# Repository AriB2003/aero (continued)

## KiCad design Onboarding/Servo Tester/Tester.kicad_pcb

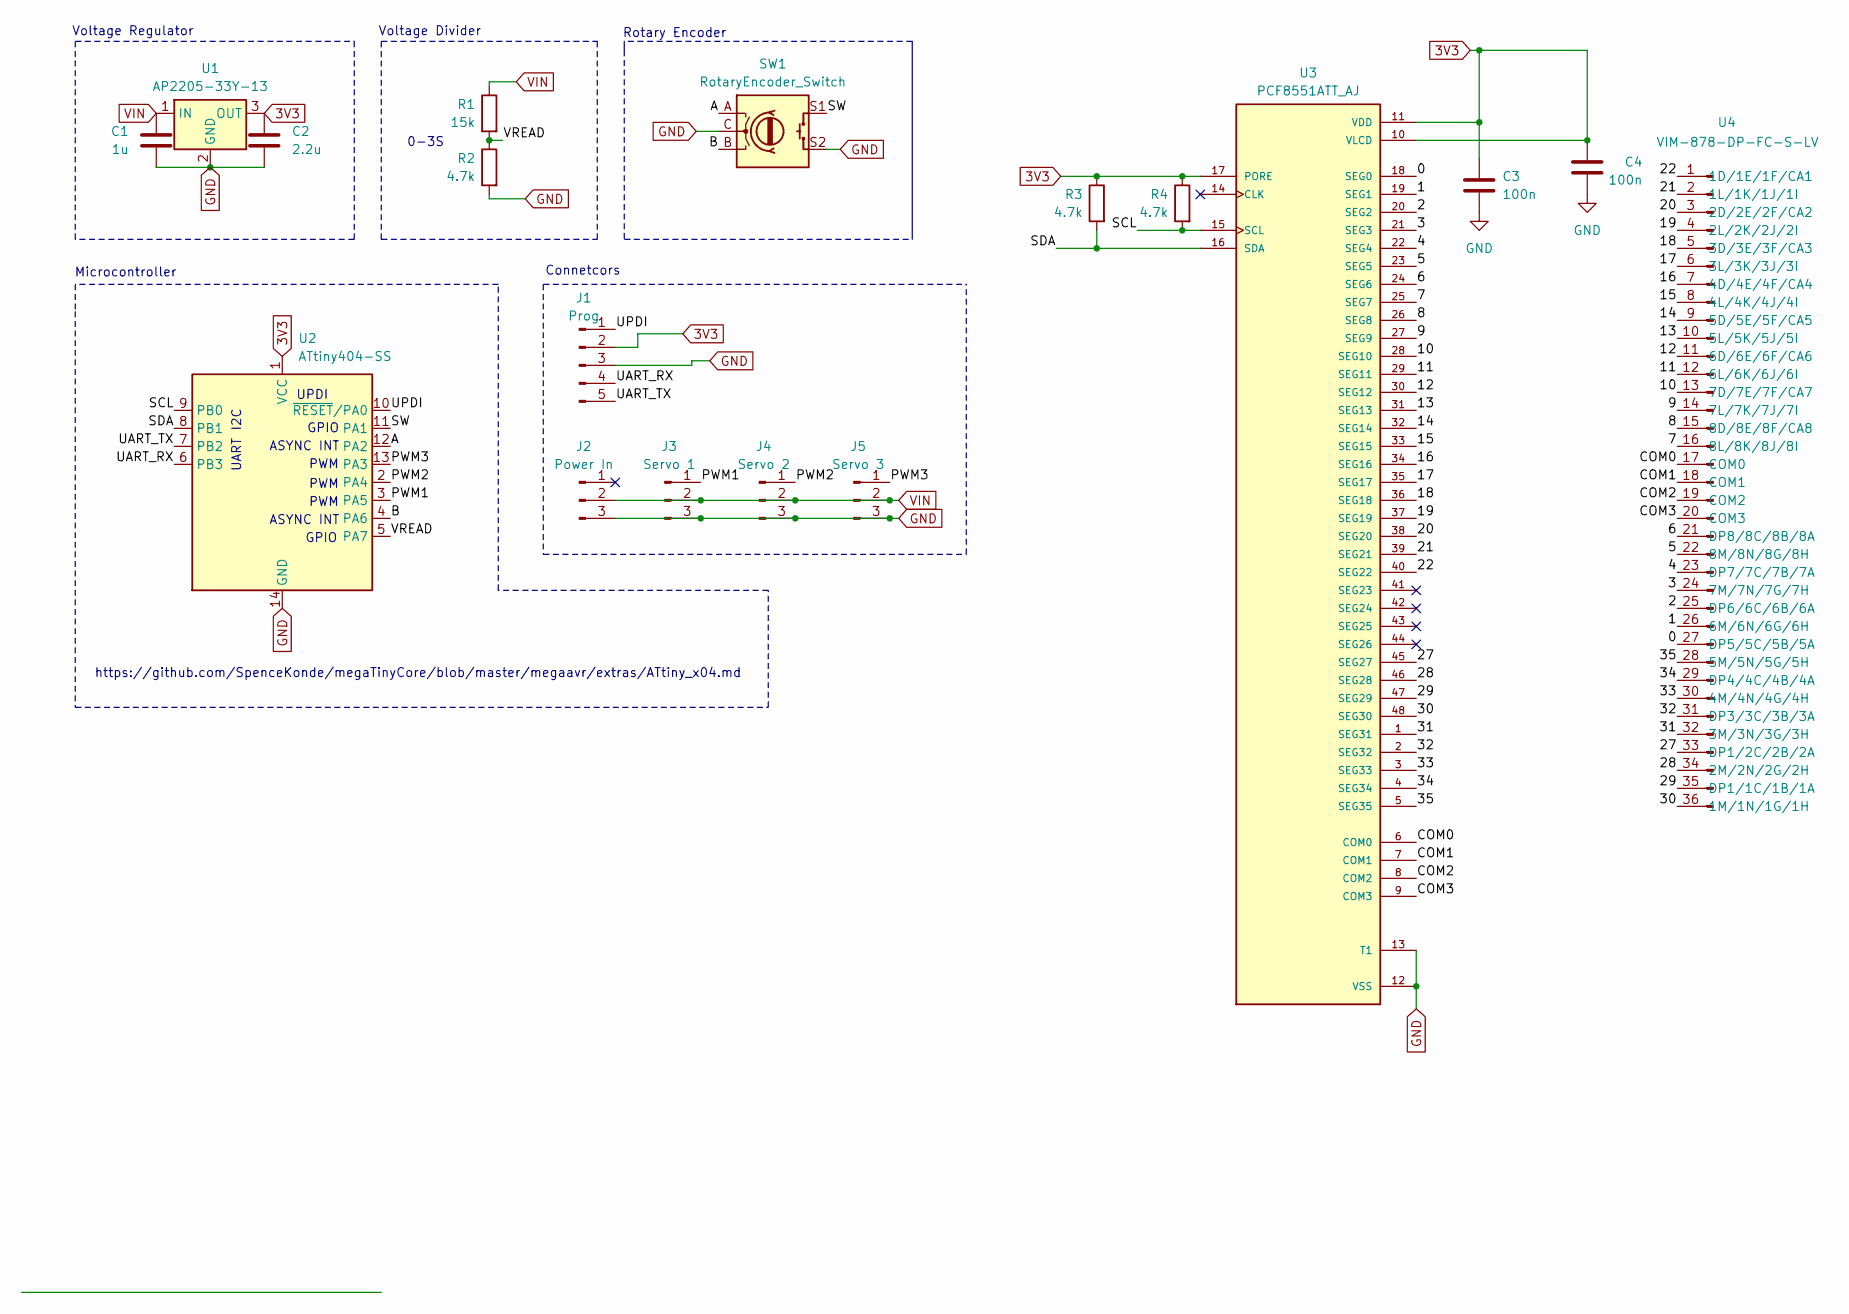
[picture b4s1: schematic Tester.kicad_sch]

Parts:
C1: 1u; C_0603_1608Metric_Pad1.08x0.95mm_HandSolder
C2: 2.2u; C_0603_1608Metric_Pad1.08x0.95mm_HandSolder
C3, C4: 100n; C_0603_1608Metric_Pad1.08x0.95mm_HandSolder
J1: Prog; PinSocket_1x05_P2.54mm_Vertical
J2: Power In; PinSocket_1x03_P2.54mm_Vertical
J3: Servo 1; PinSocket_1x03_P2.54mm_Vertical
J4: Servo 2; PinSocket_1x03_P2.54mm_Vertical
J5: Servo 3; PinSocket_1x03_P2.54mm_Vertical
R1: 15k; R_0603_1608Metric_Pad0.98x0.95mm_HandSolder
R2, R3, R4: 4.7k; R_0603_1608Metric_Pad0.98x0.95mm_HandSolder
SW1: RotaryEncoder_Switch; RotaryEncoder_Bourns_Vertical_PEC12R-3x17F-Sxxxx
U1: AP2205-33Y-13; SOT-89-3_Handsoldering
U2: ATtiny404-SS; SOIC-14_3.9x8.7mm_P1.27mm
U3: PCF8551ATT_AJ; SOP50P810X120-48N; PARTREV 2
U4: VIM-878-DP-FC-S-LV; VIM-878-DP

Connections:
3V3: C2.1, C3.1, C4.1, J1.2, R3.1, R4.1, U1.3 (OUT), U2.1 (VCC), U3.10 (VLCD), U3.11 (VDD), U3.17 (PORE)
/0: U3.18 (SEG0), U4.27 (DP5/5C/5B/5A)
/1: U3.19 (SEG1), U4.26 (6M/6N/6G/6H)
/2: U3.20 (SEG2), U4.25 (DP6/6C/6B/6A)
/3: U3.21 (SEG3), U4.24 (7M/7N/7G/7H)
/4: U3.22 (SEG4), U4.23 (DP7/7C/7B/7A)
/5: U3.23 (SEG5), U4.22 (8M/8N/8G/8H)
/6: U3.24 (SEG6), U4.21 (DP8/8C/8B/8A)
/7: U3.25 (SEG7), U4.16 (8L/8K/8J/8I)
/8: U3.26 (SEG8), U4.15 (8D/8E/8F/CA8)
/9: U3.27 (SEG9), U4.14 (7L/7K/7J/7I)
/10: U3.28 (SEG10), U4.13 (7D/7E/7F/CA7)
/11: U3.29 (SEG11), U4.12 (6L/6K/6J/6I)
/12: U3.30 (SEG12), U4.11 (6D/6E/6F/CA6)
/13: U3.31 (SEG13), U4.10 (5L/5K/5J/5I)
/14: U3.32 (SEG14), U4.9 (5D/5E/5F/CA5)
/15: U3.33 (SEG15), U4.8 (4L/4K/4J/4I)
/16: U3.34 (SEG16), U4.7 (4D/4E/4F/CA4)
/17: U3.35 (SEG17), U4.6 (3L/3K/3J/3I)
/18: U3.36 (SEG18), U4.5 (3D/3E/3F/CA3)
/19: U3.37 (SEG19), U4.4 (2L/2K/2J/2I)
/20: U3.38 (SEG20), U4.3 (2D/2E/2F/CA2)
/21: U3.39 (SEG21), U4.2 (1L/1K/1J/1I)
/22: U3.40 (SEG22), U4.1 (1D/1E/1F/CA1)
/27: U3.45 (SEG27), U4.33 (DP1/2C/2B/2A)
/28: U3.46 (SEG28), U4.34 (2M/2N/2G/2H)
/29: U3.47 (SEG29), U4.35 (DP1/1C/1B/1A)
/30: U3.48 (SEG30), U4.36 (1M/1N/1G/1H)
/31: U3.1 (SEG31), U4.32 (3M/3N/3G/3H)
/32: U3.2 (SEG32), U4.31 (DP3/3C/3B/3A)
/33: U3.3 (SEG33), U4.30 (4M/4N/4G/4H)
/34: U3.4 (SEG34), U4.29 (DP4/4C/4B/4A)
/35: U3.5 (SEG35), U4.28 (5M/5N/5G/5H)
/A: SW1.A, U2.12 (PA2)
/B: SW1.B, U2.4 (PA6)
/COM0: U3.6 (COM0), U4.17 (COM0)
/COM1: U3.7 (COM1), U4.18 (COM1)
/COM2: U3.8 (COM2), U4.19 (COM2)
/COM3: U3.9 (COM3), U4.20 (COM3)
/PWM1: J3.1, U2.3 (PA5)
/PWM2: J4.1, U2.2 (PA4)
/PWM3: J5.1, U2.13 (PA3)
/SCL: R4.2, U2.9 (PB0), U3.15 (SCL)
/SDA: R3.2, U2.8 (PB1), U3.16 (SDA)
/SW: SW1.S1, U2.11 (PA1)
/UART_RX: J1.4, U2.6 (PB3)
/UART_TX: J1.5, U2.7 (PB2)
/UPDI: J1.1, U2.10 (~RESET/PA0)
/VREAD: R1.2, R2.1, U2.5 (PA7)
GND: C1.2, C2.2, C3.2, C4.2, J1.3, J2.3, J3.3, J4.3, J5.3, R2.2, SW1.C, SW1.S2, U1.2 (GND), U2.14 (GND), U3.12 (VSS), U3.13 (T1)
VIN: C1.1, J2.2, J3.2, J4.2, J5.2, R1.1, U1.1 (IN)

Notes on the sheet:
GPIO
Voltage Divider
Connetcors
ASYNC INT
https://github.com/SpenceKonde/megaTinyCore/blob/master/megaavr/extras/ATtiny_x04.md
PWM
0-3S
Microcontroller
I2C
UPDI
Voltage Regulator
UART
Rotary Encoder

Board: 2 copper layers, 18 parts (1 on the bottom side), 51 nets, no tracks yet.

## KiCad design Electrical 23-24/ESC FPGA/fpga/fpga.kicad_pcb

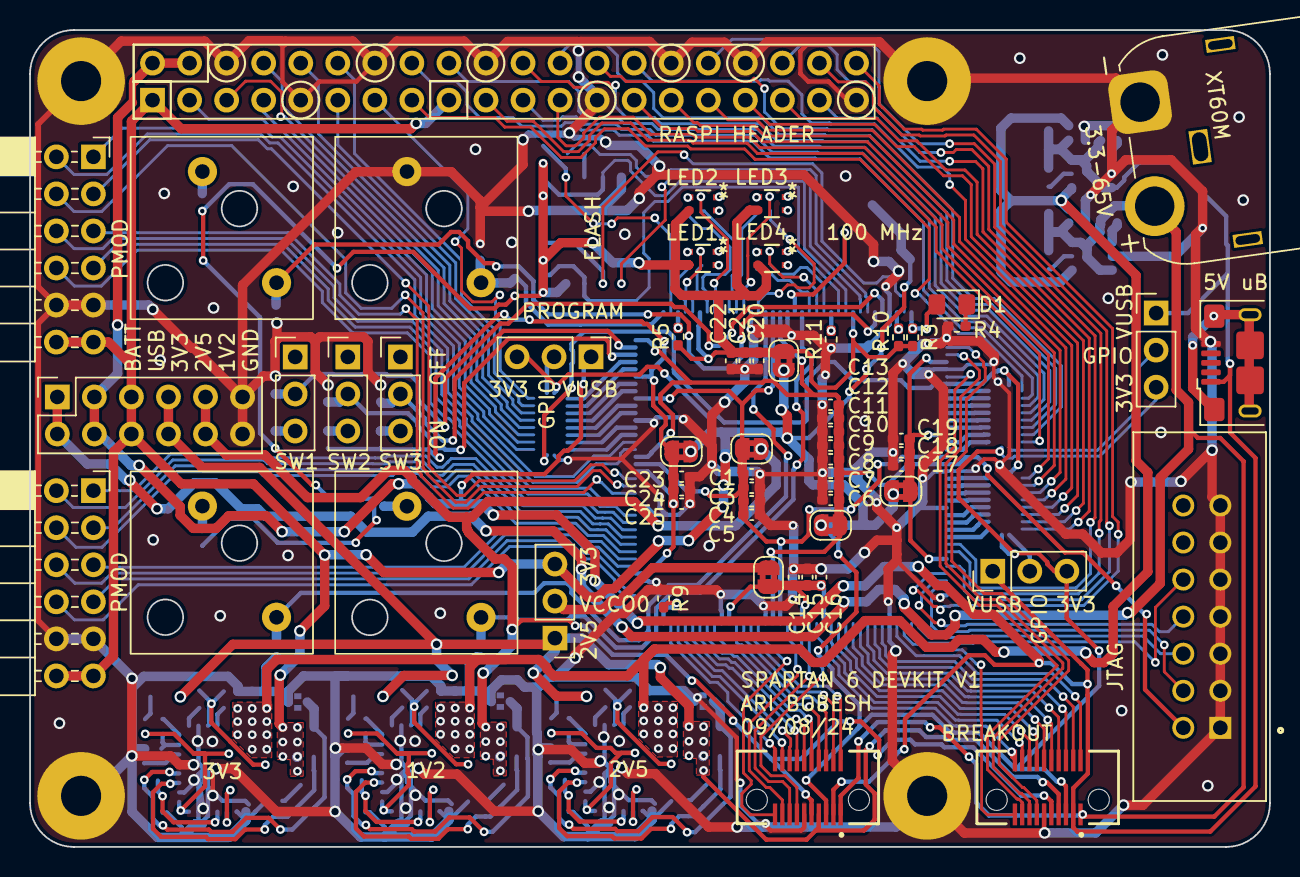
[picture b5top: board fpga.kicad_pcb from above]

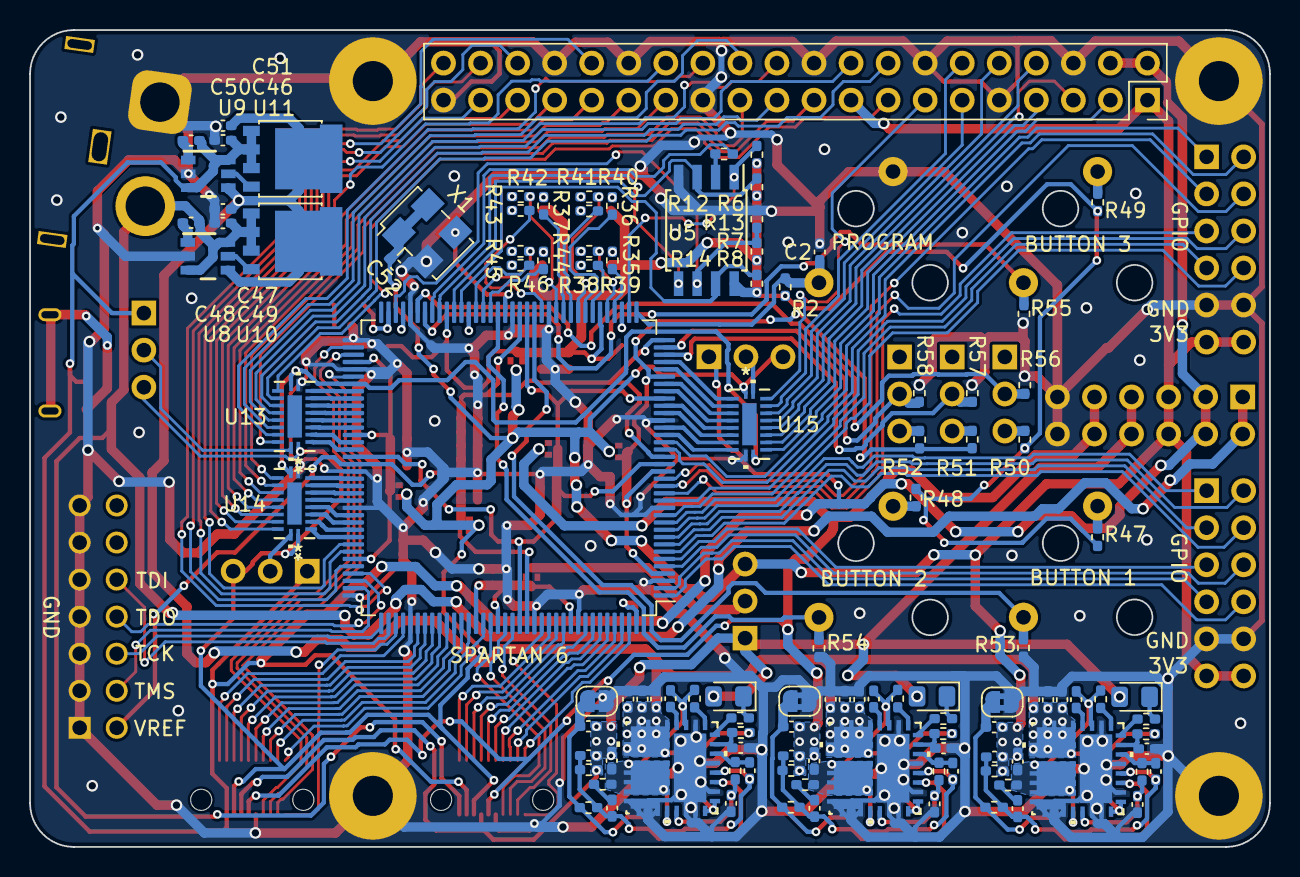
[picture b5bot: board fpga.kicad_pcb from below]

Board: 2 copper layers, 85.0 x 56.0 mm, 174 parts (113 on the bottom side), 206 nets.

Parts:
C1, C2, C3, C4, C6, C7, C8, C9, C10, C11, C12, C14, C17, C20, C23: 4.7u; C_0402_1005Metric_Pad0.74x0.62mm_HandSolder
C5, C13, C15, C16, C18, C19, C21, C22, C24, C25: 0.47u; C_0402_1005Metric_Pad0.74x0.62mm_HandSolder
C26, C33, C36, C43, C53, C60: 0.1u; C_0402_1005Metric_Pad0.74x0.62mm_HandSolder
C27, C28, C29, C37, C38, C39, C54, C55, C56: 2.2u HV; C_0402_1005Metric_Pad0.74x0.62mm_HandSolder
C30, C42, C47, C51, C59: 1u HV; C_0402_1005Metric_Pad0.74x0.62mm_HandSolder
C31, C32, C40, C41, C57, C58: 2.2u; C_0402_1005Metric_Pad0.74x0.62mm_HandSolder
C34, C44, C61: 4.7n; C_0402_1005Metric_Pad0.74x0.62mm_HandSolder
C35, C45, C62: 47u; C_0402_1005Metric_Pad0.74x0.62mm_HandSolder
C46, C49: 22n HV; C_0402_1005Metric_Pad0.74x0.62mm_HandSolder
C48, C50: 0.1u HV; C_0402_1005Metric_Pad0.74x0.62mm_HandSolder
C52: 0.01uF; C_0402_1005Metric_Pad0.74x0.62mm_HandSolder
D1, D2, D3, D4: LED; LED_0805_2012Metric_Pad1.15x1.40mm_HandSolder
J1: SBH11-PBPC-D07-ST-BK; SULLINS_SBH11-PBPC-D07-ST-BK
J2, J4: LSHM-110-04.0-L-DV-A-N-K-TR; SAMTEC_LSHM-110-04.0-L-DV-A-N-K-TR
J3: USB_B_Micro; USB_Micro-B_Amphenol_10118193-0001LF_Horizontal
J5, J6: Conn_02x06_Top_Bottom; PinSocket_2x06_P2.54mm_Horizontal
J7: Conn_02x20_Odd_Even; PinSocket_2x20_P2.54mm_Vertical
J8: Conn_02x06_Top_Bottom; PinSocket_2x06_P2.54mm_Vertical
J9: Conn_01x01_Pin; RASPI
JP1, JP2, JP3, JP4, JP5, JP6, JP7, JP8, JP9: SolderJumper_2_Bridged; SolderJumper-2_P1.3mm_Bridged2Bar_RoundedPad1.0x1.5mm
L1: 3.9u; L_0402_1005Metric_Pad0.77x0.64mm_HandSolder
L2, L3: 1.5u; L_0402_1005Metric_Pad0.77x0.64mm_HandSolder
LED1, LED2, LED3, LED4: B38G3RGB-10D0003H2U1930; B38G3RGB-10D0003H2U1930_HVK
R1, R15, R22: 1.5k; R_0402_1005Metric_Pad0.72x0.64mm_HandSolder
R2, R5: 4.7k; R_0402_1005Metric_Pad0.72x0.64mm_HandSolder
R3, R4: 330; R_0402_1005Metric_Pad0.72x0.64mm_HandSolder
R6, R21: 2.2k; R_0402_1005Metric_Pad0.72x0.64mm_HandSolder
R7, R8: 100k; R_0402_1005Metric_Pad0.72x0.64mm_HandSolder
R9, R10, R11, R13, R14, R19, R20, R27, R28, R32, R34, R53, R54, R55, R56, R57, R58: 10k; R_0402_1005Metric_Pad0.72x0.64mm_HandSolder
R12, R16, R17, R23, R25, R29, R31: 2.2; R_0402_1005Metric_Pad0.72x0.64mm_HandSolder
R18, R24, R30: 82; R_0402_1005Metric_Pad0.72x0.64mm_HandSolder
R26: 7.5k; R_0402_1005Metric_Pad0.72x0.64mm_HandSolder
R33: 3.3k; R_0402_1005Metric_Pad0.72x0.64mm_HandSolder
R35, R36, R37, R44: 270; R_0402_1005Metric_Pad0.72x0.64mm_HandSolder
R38, R39, R40, R41, R42, R43, R45, R46: 56; R_0402_1005Metric_Pad0.72x0.64mm_HandSolder
R47, R48, R49, R50, R51, R52: 1k; R_0402_1005Metric_Pad0.72x0.64mm_HandSolder
SW1, SW3, SW4, SW5, SW9, SW10, SW11: SW_SPDT; PinHeader_1x03_P2.54mm_Vertical
SW2, SW6, SW7, SW8: SW_Push; NCA1
U1: XC6SLX9-TQG144; TQFP-144_20x20mm_P0.5mm
U5: MT25QL128ABA1ESE; SOIC-8W_5.3x5.3mm_P1.27mm
U6, U7, U12: MIC28515T-E/PHA; VQFN32_PHA_MCH
U8, U9: LM74700QDBVRQ1; DBV0006A_N
U10, U11: LFPAK56
U13, U14, U15: FXMA108BQX; WQFN20_2P5X4P5_ONS
X1: KC5032Z100.000C1JX00; Oscillator_SMD_EuroQuartz_XO53-4Pin_5.0x3.2mm_HandSoldering
XT60M: XT60M; AMASS_XT60IPW-M_1x03_P7.20mm_Horizontal

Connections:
1V2: C44.1, C45.1, J2.09, J4.09, J8.9, J8.10, JP7.1 (A), L2.2, R27.1
2V5: C61.1, C62.1, D2.2 (A), D3.2 (A), D4.2 (A), J2.07, J4.07, J8.7, J8.8, L3.2, R33.1, SW1.1 (A)
3V3: C34.1, C35.1, C52.2, J2.05, J4.05, J5.11, J5.12, J6.11, J6.12, J7.1, J7.17, J8.5, J8.6, JP4.1 (A), JP5.1 (A), JP6.1 (A), JP8.1 (A), L1.2, R20.1, SW1.3 (C), SW3.3 (C), SW4.3 (C), SW5.3 (C), U13.1 (VCCA), U14.1 (VCCA), U15.1 (VCCA), X1.1 (EN), X1.4 (Vdd)
/Bank1/HSWAPEN: R9.2, U1.144 (IO_L1P_HSWAPEN_0)
/Bank2/B1: R39.2, U1.43 (IO_L62N_D6_2)
/Bank2/B2: R41.2, U1.46 (IO_L49P_D3_2)
/Bank2/B3: R43.2, U1.50 (IO_L31N_GCLK30_D15_2)
/Bank2/B4: R46.2, U1.59 (IO_L13N_D10_2)
/Bank2/BTN1: R53.2, SW6.1, U1.51 (IO_L31P_GCLK31_D14_2)
/Bank2/BTN2: R54.2, SW7.1, U1.56 (IO_L30P_GCLK1_D13_2)
/Bank2/BTN3: R55.2, SW8.1, U1.66 (IO_L2N_CMPMOSI_2)
/Bank2/G1: R38.2, U1.41 (IO_L64P_D8_2)
/Bank2/G2: R40.2, U1.45 (IO_L49N_D4_2)
/Bank2/G3: R42.2, U1.48 (IO_L48P_D7_2)
/Bank2/G4: R45.2, U1.58 (IO_L14P_D11_2)
/Bank2/INIT_B_IO: R5.2, U1.39 (IO_L65P_INIT_B_2)
/Bank2/M0_IO: R10.2, U1.69 (IO_L1N_M0_CMPMISO_2)
/Bank2/M1_IO: R11.2, U1.60 (IO_L13P_M1_2)
/Bank2/OSCI: U1.55 (IO_L30N_GCLK0_USERCCLK_2), X1.3 (OUT)
/Bank2/R1: R35.2, U1.40 (IO_L64N_D9_2)
/Bank2/R2: R36.2, U1.44 (IO_L62P_D5_2)
/Bank2/R3: R37.2, U1.47 (IO_L48N_RDWR_B_VREF_2)
/Bank2/R4: R44.2, U1.57 (IO_L14N_D12_2)
/Bank2/SPI_MISO1_IO: R12.2, U1.65 (IO_L3P_D0_DIN_MISO_MISO1_2)
/Bank2/SW1: R56.2, SW9.2 (B), U1.67 (IO_L2P_CMPCLK_2)
/Bank2/SW2: R57.2, SW10.2 (B), U1.34 (IO_L1N_VREF_3)
/Bank2/SW3: R58.2, SW11.2 (B), U1.35 (IO_L1P_3)
/Program/DONE: D1.2 (A), R3.1, U1.71 (DONE_2)
/Regulators/FB1: C33.2, C34.2, R20.2, R21.1, U6.27 (FB)
/Regulators/FB2: C43.2, C44.2, R27.2, R28.1, U7.27 (FB)
/Regulators/FB3: C60.2, C61.2, R33.2, R34.1, U12.27 (FB)
/Regulators/SW1: C26.1, L1.1, R15.1, R19.1, U6.3 (SW), U6.12 (SW), U6.13 (SW), U6.14 (SW), U6.15 (SW), U6.20 (SW)
/Regulators/SW2: C36.1, L2.1, R22.1, R26.1, U7.3 (SW), U7.12 (SW), U7.13 (SW), U7.14 (SW), U7.15 (SW), U7.20 (SW)
/Regulators/SW3: C53.1, L3.1, R1.1, R32.1, U12.3 (SW), U12.12 (SW), U12.13 (SW), U12.14 (SW), U12.15 (SW), U12.20 (SW)
/Regulators/VDD1: C32.2, R17.2, U6.30 (VDD)
/Regulators/VDD2: C41.2, R23.2, U7.30 (VDD)
/Regulators/VIN: C27.2, C28.2, C29.2, C37.2, C38.2, C39.2, C47.1, C51.1, C54.2, C55.2, C56.2, R16.2, R25.2, R31.2, U6.5 (VIN), U6.6 (VIN), U6.7 (VIN), U6.8 (VIN), U6.9 (VIN), U6.10 (VIN), U6.11 (VIN), U6.24 (EN), U6.25 (FREQ), U7.5 (VIN), U7.6 (VIN), U7.7 (VIN), U7.8 (VIN), U7.9 (VIN), U7.10 (VIN), U7.11 (VIN), U7.24 (EN), U7.25 (FREQ), U8.4 (CATHODE), U9.4 (CATHODE), U10.5 (D), U11.5 (D), U12.5 (VIN), U12.6 (VIN), U12.7 (VIN), U12.8 (VIN), U12.9 (VIN), U12.10 (VIN), U12.11 (VIN), U12.24 (EN), U12.25 (FREQ)
GND: C1.2, C2.2, C3.2, C4.2, C5.2, C6.2, C7.2, C8.2, C9.2, C10.2, C11.2, C12.2, C13.2, C14.2, C15.2, C16.2, C17.2, C18.2, C19.2, C20.2, C21.2, C22.2, C23.2, C24.2, C25.2, C27.1, C28.1, C29.1, C30.1, C31.1, C37.1, C38.1, C39.1, C40.1, C42.1, C46.2, C47.2, C49.2, C51.2, C52.1, C54.1, C55.1, C56.1, C57.1, C59.1, J1.1, J1.3, J1.5, J1.7, J1.9, J1.11, J1.13, J2.11, J3.5 (GND), J4.11, J5.9, J5.10, J6.9, J6.10, J7.6, J7.9, J7.14, J7.20, J7.25, J7.30, J7.34, J7.39, J8.11, J8.12, J9.1, JP1.2 (B), JP2.2 (B), JP3.2 (B), R4.2, R7.1, R9.1, R11.1, R53.1, R54.1, R55.1, R56.1, R57.1, R58.1, SW2.2, U1.3 (GND), U1.13 (GND), U1.25 (GND), U1.49 (GND), U1.54 (GND), U1.68 (GND), U1.73 (SUSPEND), U1.77 (GND), U1.91 (GND), U1.96 (GND), U1.108 (GND), U1.113 (GND), U1.130 (GND), U1.136 (GND), U5.4 (VSS), U6.2 (PGND), U6.16 (PGND), U6.17 (PGND), U6.18 (PGND), U6.19 (PGND), U6.22 (PGND), U6.23 (EXTVDD), U6.26 (MODE), U6.29 (PGND), U6.33 (PGND), U7.2 (PGND), U7.16 (PGND), U7.17 (PGND), U7.18 (PGND), U7.19 (PGND), U7.22 (PGND), U7.23 (EXTVDD), U7.26 (MODE), U7.29 (PGND), U7.33 (PGND), U8.2 (GND), U9.2 (GND), U12.2 (PGND), U12.16 (PGND), U12.17 (PGND), U12.18 (PGND), U12.19 (PGND), U12.22 (PGND), U12.23 (EXTVDD), U12.26 (MODE), U12.29 (PGND), U12.33 (PGND), U13.10 (GND), U14.10 (GND), U15.10 (GND), X1.2 (GND), XT60M.1 (-)
GND1: C32.1, C35.2, JP1.1 (A), R21.2, U6.28 (AGND)
GND2: C41.1, C45.2, JP2.1 (A), R28.2, U7.28 (AGND)
GND3: C58.1, C62.2, JP3.1 (A), R34.2, U12.28 (AGND)
GPIO0: J7.27, U14.13 (B6)
GPIO1: J7.28, U14.16 (B3)
GPIO2: J7.3, U15.12 (B7)
GPIO3: J7.5, U15.14 (B5)
GPIO4: J7.7, U15.13 (B6)
GPIO5: J7.29, U14.14 (B5)
GPIO6: J7.31, U14.15 (B4)
GPIO7: J7.26, U13.18 (B1)
GPIO8: J7.24, U13.17 (B2)
GPIO9: J7.21, U13.14 (B5)
GPIO10: J7.19, U13.19 (B0)
GPIO11: J7.23, U14.12 (B7)
GPIO12: J7.32, U1.102 (IO_L32P_1)
GPIO13: J7.33, U14.17 (B2)
GPIO14: J7.8, U15.15 (B4)
GPIO15: J7.10, U15.16 (B3)
GPIO16: J7.36, U1.101 (IO_L32N_1)
GPIO17: J7.11, U15.17 (B2)
GPIO18: J7.12, U15.18 (B1)
GPIO19: J7.35, U14.18 (B1)
GPIO20: J7.38, U1.104 (IO_L1N_VREF_1)
GPIO21: J7.40, U1.105 (IO_L1P_1)
GPIO22: J7.15, U13.12 (B7)
GPIO23: J7.16, U13.13 (B6)
GPIO24: J7.18, U13.15 (B4)
GPIO25: J7.22, U13.16 (B3)
GPIO26: J7.37, U14.19 (B0)
GPIO27: J7.13, U15.19 (B0)
unnamed: C33.1, R19.2
unnamed: C43.1, R26.2
unnamed: C60.1, R32.2
unnamed: D1.1 (K), R4.1
unnamed: D2.1 (K), R18.1
unnamed: D3.1 (K), R24.1
unnamed: D4.1 (K), R30.1
unnamed: JP9.2 (B), SW1.2 (B)
unnamed: LED1.1, R38.1
unnamed: LED1.2, R39.1
unnamed: LED1.4, R35.1
unnamed: LED2.1, R40.1
unnamed: LED2.2, R41.1
unnamed: LED2.4, R36.1
unnamed: LED3.1, R42.1
unnamed: LED3.2, R43.1
unnamed: LED3.4, R37.1
unnamed: LED4.1, R45.1
unnamed: LED4.2, R46.1
unnamed: LED4.4, R44.1
unnamed: R47.1, SW6.2
unnamed: R48.1, SW7.2
unnamed: R49.1, SW8.2
unnamed: SW3.2 (B), U13.20 (VCCB)
unnamed: SW4.2 (B), U14.20 (VCCB)
unnamed: SW5.2 (B), U15.20 (VCCB)
unnamed: R50.1, SW9.3 (C)
unnamed: R51.1, SW10.3 (C)
unnamed: R52.1, SW11.3 (C)
unnamed: J2.20, U1.143 (IO_L1N_VREF_0)
unnamed: J2.16, U1.141 (IO_L2N_0)
unnamed: J2.18, U1.142 (IO_L2P_0)
unnamed: J2.12, U1.139 (IO_L3N_0)
unnamed: J2.14, U1.140 (IO_L3P_0)
unnamed: J2.08, U1.137 (IO_L4N_0)
unnamed: J2.10, U1.138 (IO_L4P_0)
unnamed: J2.04, U1.133 (IO_L34N_GCLK18_0)
unnamed: J2.06, U1.134 (IO_L34P_GCLK19_0)
unnamed: J2.19, U1.131 (IO_L35N_GCLK16_0)
unnamed: J2.02, U1.132 (IO_L35P_GCLK17_0)
unnamed: J2.15, U1.126 (IO_L36N_GCLK14_0)
unnamed: J2.17, U1.127 (IO_L36P_GCLK15_0)
unnamed: J4.20, U1.123 (IO_L37N_GCLK12_0)
unnamed: J2.13, U1.124 (IO_L37P_GCLK13_0)
unnamed: J4.17, U1.78 (IO_L47N_1)
unnamed: J4.16, U1.120 (IO_L62N_VREF_0)
unnamed: J4.18, U1.121 (IO_L62P_0)
unnamed: J4.12, U1.118 (IO_L63N_SCP6_0)
unnamed: J4.14, U1.119 (IO_L63P_SCP7_0)
unnamed: J4.08, U1.116 (IO_L64N_SCP4_0)
unnamed: J4.10, U1.117 (IO_L64P_SCP5_0)
unnamed: J4.04, U1.114 (IO_L65N_SCP2_0)
unnamed: J4.06, U1.115 (IO_L65P_SCP3_0)
unnamed: J4.19, U1.111 (IO_L66N_SCP0_0)
unnamed: J4.02, U1.112 (IO_L66P_SCP1_0)
unnamed: J4.13, U1.74 (IO_L74N_DOUT_BUSY_1)
unnamed: J4.15, U1.75 (IO_L74P_AWAKE_1)
unnamed: C2.1, R2.2, SW2.1, U1.37 (PROGRAM_B_2)
unnamed: C26.2, U6.4 (BST)
unnamed: R15.2, U6.1 (ILIM)
unnamed: R18.2, U6.32 (PG)
unnamed: C31.2, R17.1, U6.21 (PVDD)
unnamed: C30.2, R16.1, U6.31 (SVIN)
unnamed: C36.2, U7.4 (BST)
unnamed: R22.2, U7.1 (ILIM)
unnamed: R24.2, U7.32 (PG)
unnamed: C40.2, R23.1, U7.21 (PVDD)
unnamed: C42.2, R25.1, U7.31 (SVIN)
unnamed: C48.2, U8.1 (VCAP)
unnamed: C50.2, U9.1 (VCAP)
unnamed: U8.5 (GATE), U10.4 (G)
unnamed: U9.5 (GATE), U11.4 (G)
unnamed: C53.2, U12.4 (BST)
unnamed: R1.2, U12.1 (ILIM)
unnamed: R30.2, U12.32 (PG)
unnamed: C57.2, R29.1, U12.21 (PVDD)
unnamed: C59.2, R31.1, U12.31 (SVIN)
unnamed: C58.2, R29.2, U12.30 (VDD)
unnamed: U1.88 (IO_L42P_GCLK7_1), U13.2 (A0)
unnamed: U1.87 (IO_L42N_GCLK6_TRDY1_1), U13.3 (A1)
unnamed: U1.85 (IO_L43P_GCLK5_1), U13.4 (A2)
unnamed: U1.84 (IO_L43N_GCLK4_1), U13.5 (A3)
unnamed: U1.83 (IO_L45P_1), U13.6 (A4)
unnamed: U1.82 (IO_L45N_1), U13.7 (A5)
unnamed: U1.81 (IO_L46P_1), U13.8 (A6)
unnamed: U1.80 (IO_L46N_1), U13.9 (A7)
unnamed: U1.100 (IO_L33P_1), U14.2 (A0)
unnamed: U1.99 (IO_L33N_1), U14.3 (A1)
unnamed: U1.98 (IO_L34P_1), U14.4 (A2)
unnamed: U1.97 (IO_L34N_1), U14.5 (A3)
unnamed: U1.95 (IO_L40P_GCLK11_1), U14.6 (A4)
unnamed: U1.94 (IO_L40N_GCLK10_1), U14.7 (A5)
unnamed: U1.93 (IO_L41P_GCLK9_IRDY1_1), U14.8 (A6)
unnamed: U1.92 (IO_L41N_GCLK8_1), U14.9 (A7)
unnamed: U1.33 (IO_L2P_3), U15.2 (A0)
unnamed: U1.32 (IO_L2N_3), U15.3 (A1)
unnamed: U1.30 (IO_L36P_3), U15.4 (A2)
unnamed: U1.29 (IO_L36N_3), U15.5 (A3)
unnamed: U1.27 (IO_L37P_3), U15.6 (A4)
unnamed: U1.26 (IO_L37N_3), U15.7 (A5)
unnamed: U1.24 (IO_L41P_GCLK27_3), U15.8 (A6)
unnamed: U1.23 (IO_L41N_GCLK26_3), U15.9 (A7)
OE: U1.79 (IO_L47P_1), U13.11 (/OE), U14.11 (/OE), U15.11 (/OE)
PMOD1_0: J5.1, U1.22 (IO_L42P_GCLK25_TRDY2_3)
PMOD1_1: J5.3, U1.17 (IO_L43P_GCLK23_3)
PMOD1_2: J5.5, U1.15 (IO_L44P_GCLK21_3)
PMOD1_3: J5.7, U1.12 (IO_L49P_3)
PMOD1_4: J5.2, U1.21 (IO_L42N_GCLK24_3)
PMOD1_5: J5.4, U1.16 (IO_L43N_GCLK22_IRDY2_3)
PMOD1_6: J5.6, U1.14 (IO_L44N_GCLK20_3)
PMOD1_7: J5.8, U1.11 (IO_L49N_3)
PMOD2_0: J6.1, U1.10 (IO_L50P_3)
PMOD2_1: J6.3, U1.8 (IO_L51P_3)
PMOD2_2: J6.5, U1.6 (IO_L52P_3)
PMOD2_3: J6.7, U1.2 (IO_L83P_3)
PMOD2_4: J6.2, U1.9 (IO_L50N_3)
PMOD2_5: J6.4, U1.7 (IO_L51N_3)
PMOD2_6: J6.6, U1.5 (IO_L52N_3)
PMOD2_7: J6.8, U1.1 (IO_L83N_VREF_3)
SPI_CLK: R7.2, R8.1, U1.70 (IO_L1P_CCLK_2), U5.6 (C)
SPI_CS: R6.2, U1.38 (IO_L65N_CSO_B_2), U5.1 (~S)
SPI_MISO1: R12.1, U5.2 (DQ1)
SPI_MISO2: R13.2, U1.62 (IO_L12P_D1_MISO2_2), U5.3 (~W/DQ2)
SPI_MISO3: R14.2, U1.61 (IO_L12N_D2_MISO3_2), U5.7 (~HOLD/DQ3)
SPI_MOSI/MISO0: U1.64 (IO_L3N_MOSI_CSI_B_MISO0_2), U5.5 (DQ0)
TCK: J1.6, U1.109 (TCK)
TDI: J1.10, U1.110 (TDI)
TDO: J1.8, U1.106 (TDO)
TMS: J1.4, U1.107 (TMS)
VBATT: C48.1, C49.1, J2.01, J4.01, J8.1, J8.2, U8.3 (EN), U8.6 (ANODE), U10.1 (S), U10.2 (S), U10.3 (S), XT60M.2 (+)
VCCO_0: C14.1, C15.1, C16.1, JP9.1 (A), U1.122 (VCCO_0), U1.125 (VCCO_0), U1.135 (VCCO_0)
VCCO_1: C17.1, C18.1, C19.1, JP4.2 (B), U1.76 (VCCO_1), U1.86 (VCCO_1), U1.103 (VCCO_1)
VCCO_2: C20.1, C21.1, C22.1, JP6.2 (B), LED1.3, LED2.3, LED3.3, LED4.3, R2.1, R3.2, R5.1, R6.1, R8.2, R10.1, R13.1, R14.1, R47.2, R48.2, R49.2, R50.2, U1.42 (VCCO_2), U1.63 (VCCO_2), U5.8 (VCC)
VCCO_3: C23.1, C24.1, C25.1, JP5.2 (B), R51.2, R52.2, U1.4 (VCCO_3), U1.18 (VCCO_3), U1.31 (VCCO_3)
VCC_AUX: C6.1, C7.1, C8.1, C9.1, C10.1, C11.1, C12.1, C13.1, J1.2, JP8.2 (B), U1.20 (VCCAUX), U1.36 (VCCAUX), U1.53 (VCCAUX), U1.90 (VCCAUX), U1.129 (VCCAUX)
VCC_INT: C1.1, C3.1, C4.1, C5.1, JP7.2 (B), U1.19 (VCCINT), U1.28 (VCCINT), U1.52 (VCCINT), U1.89 (VCCINT), U1.128 (VCCINT)
VUSB: C46.1, C50.1, J2.03, J3.1 (VBUS), J4.03, J7.2, J7.4, J8.3, J8.4, SW3.1 (A), SW4.1 (A), SW5.1 (A), U9.3 (EN), U9.6 (ANODE), U11.1 (S), U11.2 (S), U11.3 (S)

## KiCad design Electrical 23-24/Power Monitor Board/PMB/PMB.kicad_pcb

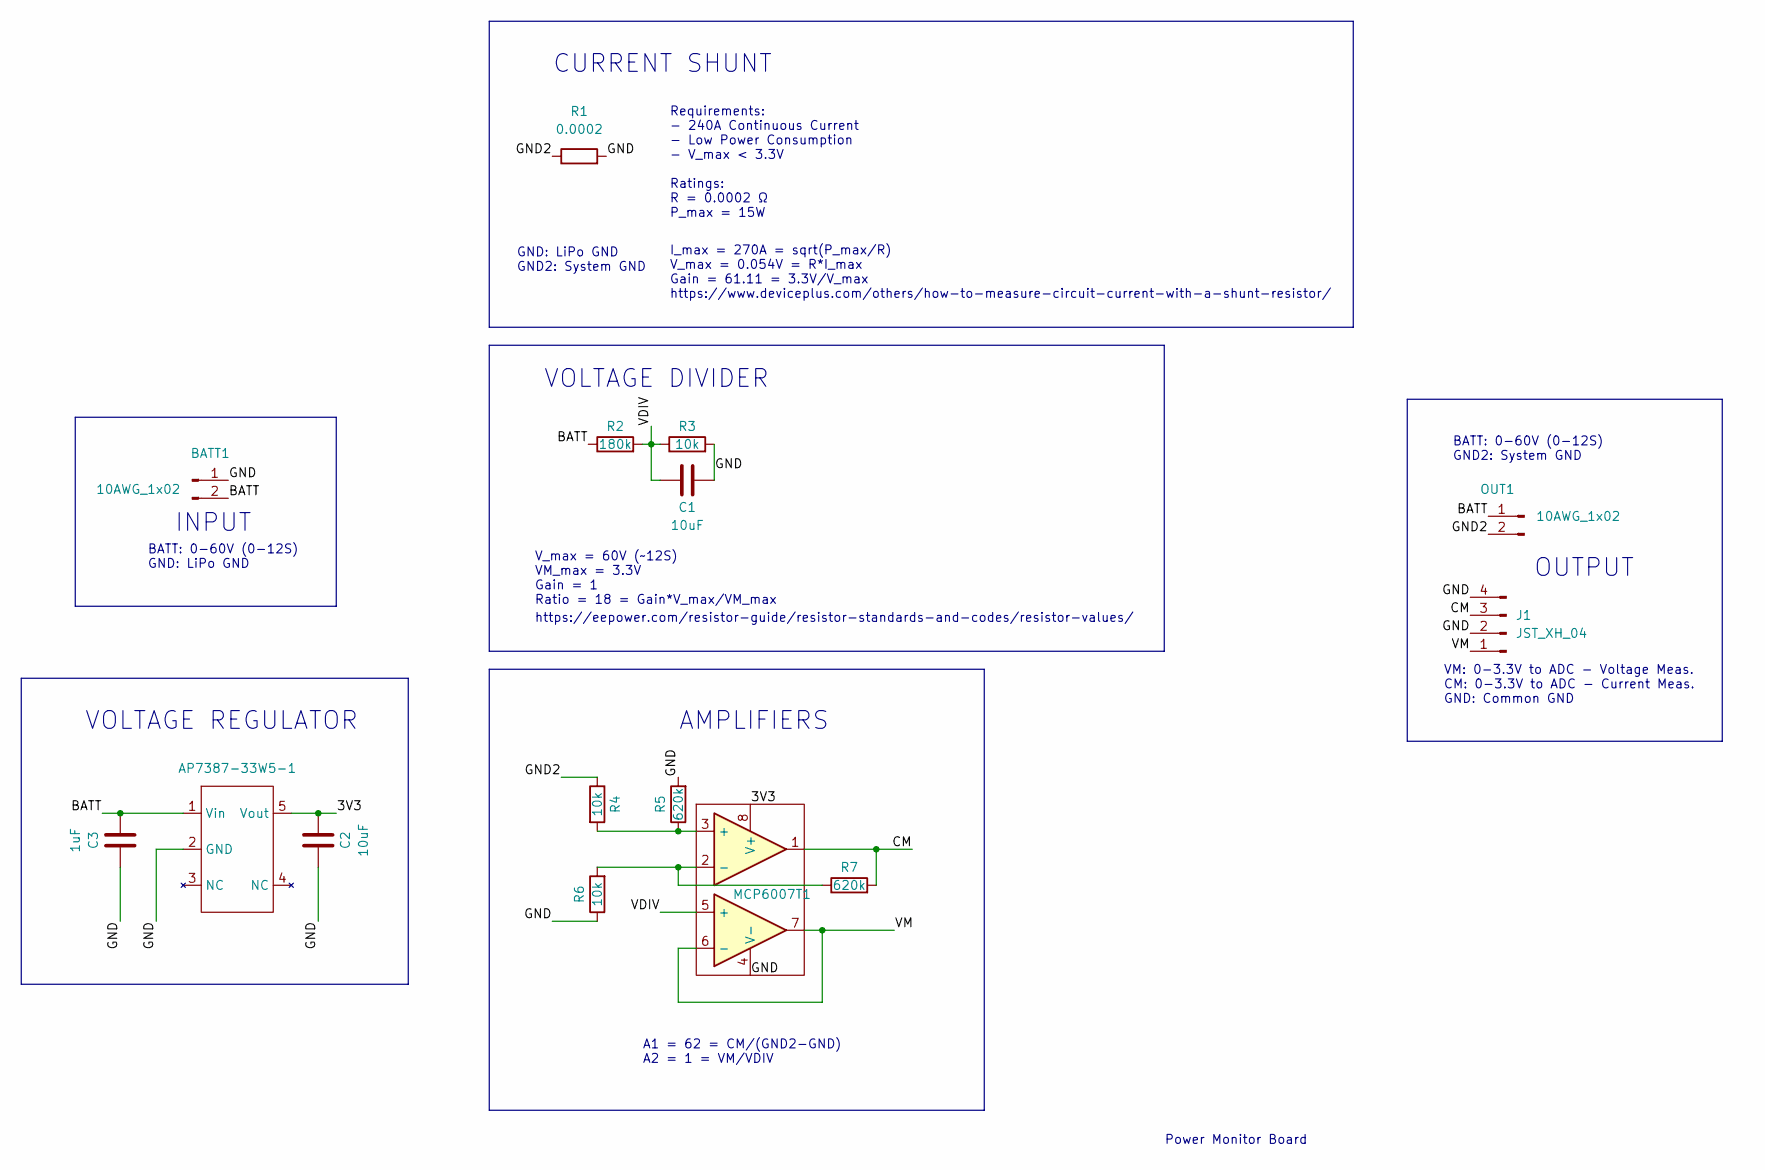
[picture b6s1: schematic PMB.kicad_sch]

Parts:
AP7387-33W5-1: SOT-23-5_HandSoldering
BATT1: 10AWG_1x02; Power
C1, C2: 10uF; C_0603_1608Metric_Pad1.08x0.95mm_HandSolder
C3: 1uF; C_0603_1608Metric_Pad1.08x0.95mm_HandSolder
J1: JST_XH_04; JST_XH_S4B-XH-A_1x04_P2.50mm_Horizontal
MCP6007T1: TSSOP-8_3x3mm_P0.65mm
OUT1: 10AWG_1x02; Power
R1: 0.0002; 6030_15075Metric_Pad4.20x7.60mm_HandSolder
R2: 180k; R_0603_1608Metric_Pad0.98x0.95mm_HandSolder
R3, R4, R6: 10k; R_0603_1608Metric_Pad0.98x0.95mm_HandSolder
R5, R7: 620k; R_0603_1608Metric_Pad0.98x0.95mm_HandSolder

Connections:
/3V3: AP7387-33W5-1.5 (Vout), C2.2, MCP6007T1.8 (V+)
/BATT: AP7387-33W5-1.1 (Vin), BATT1.2, C3.1, OUT1.1, R2.1
/CM: J1.3, MCP6007T1.1, R7.2
/GND: AP7387-33W5-1.2 (GND), BATT1.1, C1.2, C2.1, C3.2, J1.2, J1.4, MCP6007T1.4 (V-), R1.2, R3.2, R5.2, R6.1
/GND2: OUT1.2, R1.1, R4.1
/VDIV: C1.1, MCP6007T1.5 (+), R2.2, R3.1
/VM: J1.1, MCP6007T1.6 (-), MCP6007T1.7
unnamed: MCP6007T1.3 (+), R4.2, R5.1
unnamed: MCP6007T1.2 (-), R6.2, R7.1

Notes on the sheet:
VOLTAGE REGULATOR
GND: LiPo GND GND2: System GND
BATT: 0-60V (0-12S) GND: LiPo GND
V_max = 60V (~12S) VM_max = 3.3V Gain = 1 Ratio = 18 = Gain*V_max/VM_max
INPUT
OUTPUT
Power Monitor Board
VM: 0-3.3V to ADC - Voltage Meas. CM: 0-3.3V to ADC - Current Meas. GND: Common GND
BATT: 0-60V (0-12S) GND2: System GND
VOLTAGE DIVIDER
AMPLIFIERS
A1 = 62 = CM/(GND2-GND) A2 = 1 = VM/VDIV
I_max = 270A = sqrt(P_max/R) V_max = 0.054V = R*I_max Gain = 61.11 = 3.3V/V_max https://www.deviceplus.com/others/how-to-measure-circuit-current-with-a-shunt-resistor/
Requirements: - 240A Continuous Current - Low Power Consumption - V_max < 3.3V Ratings: R = 0.0002 Ω P_max = 15W
CURRENT SHUNT
https://eepower.com/resistor-guide/resistor-standards-and-codes/resistor-values/

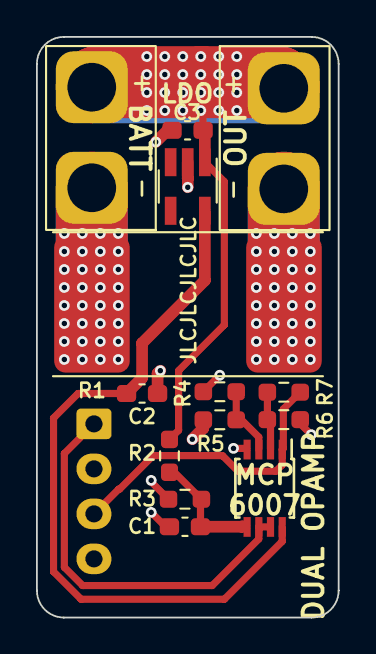
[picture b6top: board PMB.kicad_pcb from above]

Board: 2 copper layers, 16.8 x 32.3 mm, 15 parts (1 on the bottom side), 9 nets.

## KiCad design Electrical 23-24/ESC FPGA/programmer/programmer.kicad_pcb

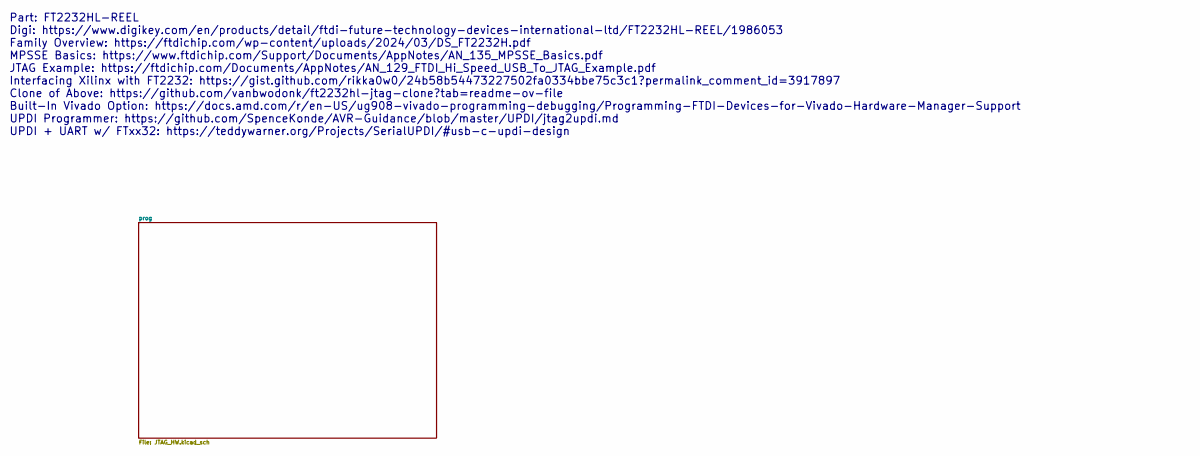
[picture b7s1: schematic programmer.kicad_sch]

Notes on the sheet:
Part: FT2232HL-REEL Digi: https://www.digikey.com/en/products/detail/ftdi-future-technology-devices-international-ltd/FT2232HL-REEL/1986053 Family Overview: https://ftdichip.com/wp-content/uploads/2024/03/DS_FT2232H.pdf MPSSE Basics: https://www.ftdichip.com/Support/Documents/AppNotes/AN_135_MPSSE_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
